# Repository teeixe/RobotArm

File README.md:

# RobotArm
Braço Robo de Cinco Articulações

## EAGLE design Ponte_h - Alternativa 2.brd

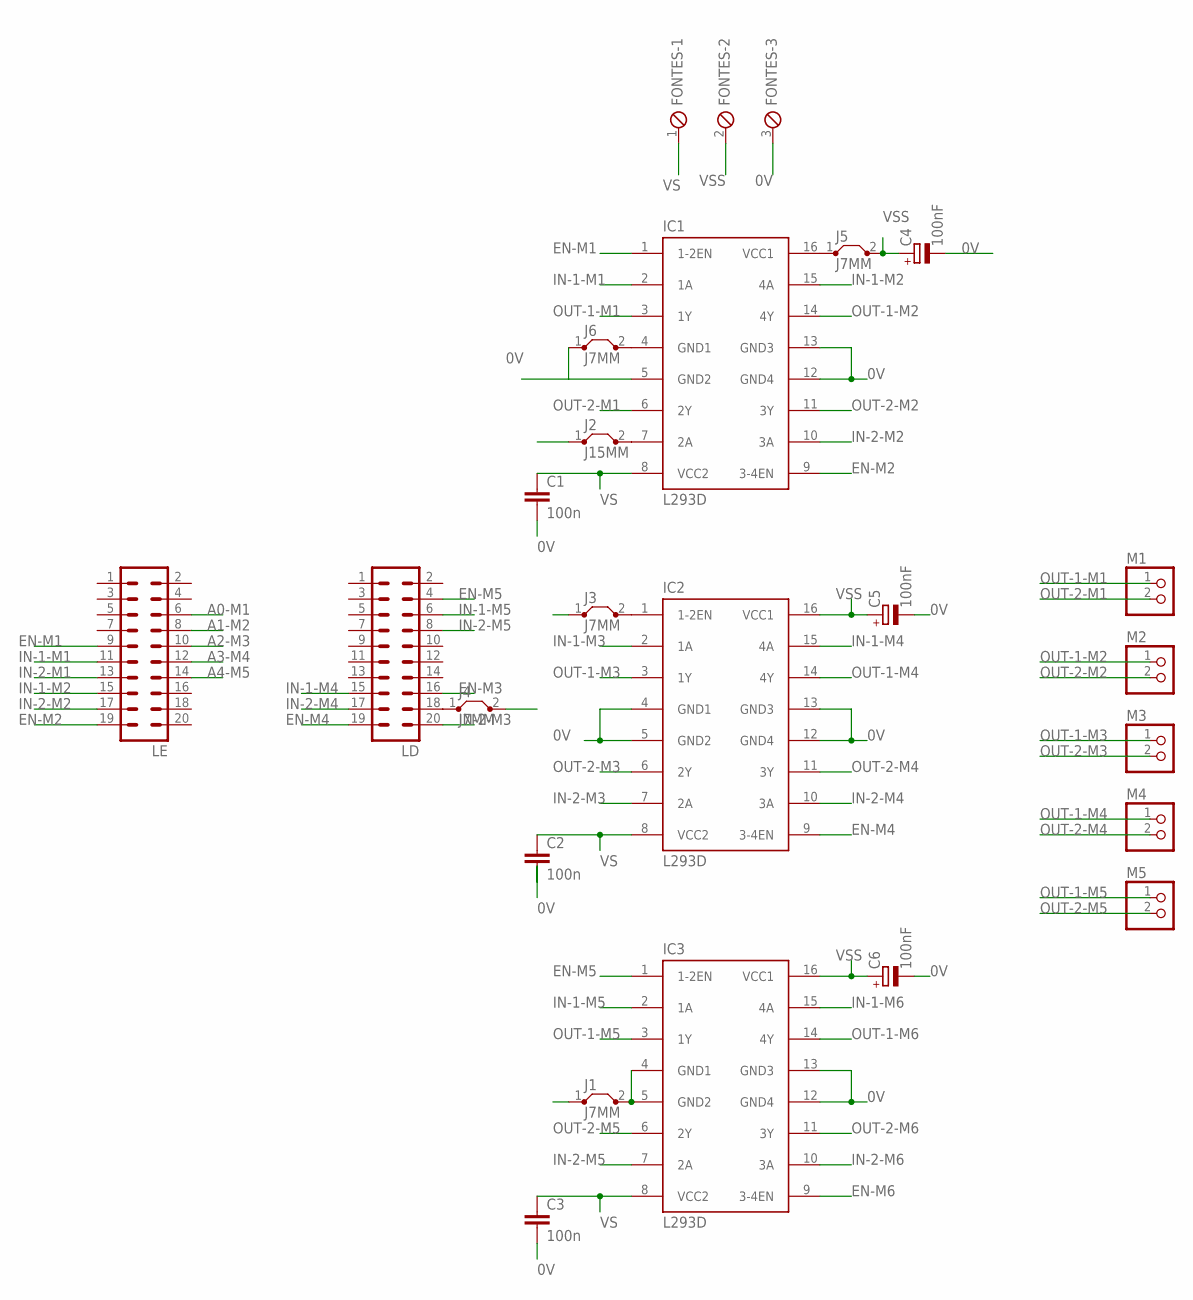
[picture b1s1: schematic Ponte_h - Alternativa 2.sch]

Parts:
C1, C2, C3: 100n; C7.5B3
C4, C5, C6: 100nF; E1,8-4
FONTES: MPT3; 3POL254
IC1, IC2, IC3: L293D; DIL16
J1, J3, J4, J5, J6: J7MM; 07
J2: J15MM; 15
LD: MA10-2
LE: MA10-2
M1, M2, M3, M4, M5: PINHD-1X2; 1X02

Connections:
0V: C1.2, C2.2, C3.2, C4.-, C5.-, C6.-, FONTES.3, IC1.5 (GND2), IC1.12 (GND4), IC1.13 (GND3), IC2.4 (GND1), IC2.5 (GND2), IC2.12 (GND4), IC2.13 (GND3), IC3.12 (GND4), IC3.13 (GND3), J1.1, J6.1
A0-M1: LE.6
A1-M2: LE.8
A2-M3: LE.10
A3-M4: LE.12
A4-M5: LE.14
EN-M1: IC1.1 (1-2EN), LE.9
EN-M2: IC1.9 (3-4EN), LE.19
EN-M3: J3.1, J4.2, LD.16
EN-M4: IC2.9 (3-4EN), LD.19
EN-M5: IC3.1 (1-2EN), LD.4
EN-M6: IC3.9 (3-4EN)
IN-1-M1: IC1.2 (1A), LE.11
IN-1-M2: IC1.15 (4A), LE.15
IN-1-M3: IC2.2 (1A)
IN-1-M4: IC2.15 (4A), LD.15
IN-1-M5: IC3.2 (1A), LD.6
IN-1-M6: IC3.15 (4A)
IN-2-M1: J2.1, LE.13
IN-2-M2: IC1.10 (3A), LE.17
IN-2-M3: IC2.7 (2A), LD.20
IN-2-M4: IC2.10 (3A), LD.17
IN-2-M5: IC3.7 (2A), LD.8
IN-2-M6: IC3.10 (3A)
unnamed: IC1.7 (2A), J2.2
unnamed: IC3.4 (GND1), IC3.5 (GND2), J1.2
unnamed: IC2.1 (1-2EN), J3.2
unnamed: J4.1, LD.18
unnamed: IC1.16 (VCC1), J5.1
unnamed: IC1.4 (GND1), J6.2
OUT-1-M1: IC1.3 (1Y), M1.1
OUT-1-M2: IC1.14 (4Y), M2.1
OUT-1-M3: IC2.3 (1Y), M3.1
OUT-1-M4: IC2.14 (4Y), M4.1
OUT-1-M5: IC3.3 (1Y), M5.1
OUT-1-M6: IC3.14 (4Y)
OUT-2-M1: IC1.6 (2Y), M1.2
OUT-2-M2: IC1.11 (3Y), M2.2
OUT-2-M3: IC2.6 (2Y), M3.2
OUT-2-M4: IC2.11 (3Y), M4.2
OUT-2-M5: IC3.6 (2Y), M5.2
OUT-2-M6: IC3.11 (3Y)
VS: C1.1, C2.1, C3.1, FONTES.1, IC1.8 (VCC2), IC2.8 (VCC2), IC3.8 (VCC2)
VSS: C4.+, C5.+, C6.+, FONTES.2, IC2.16 (VCC1), IC3.16 (VCC1), J5.2

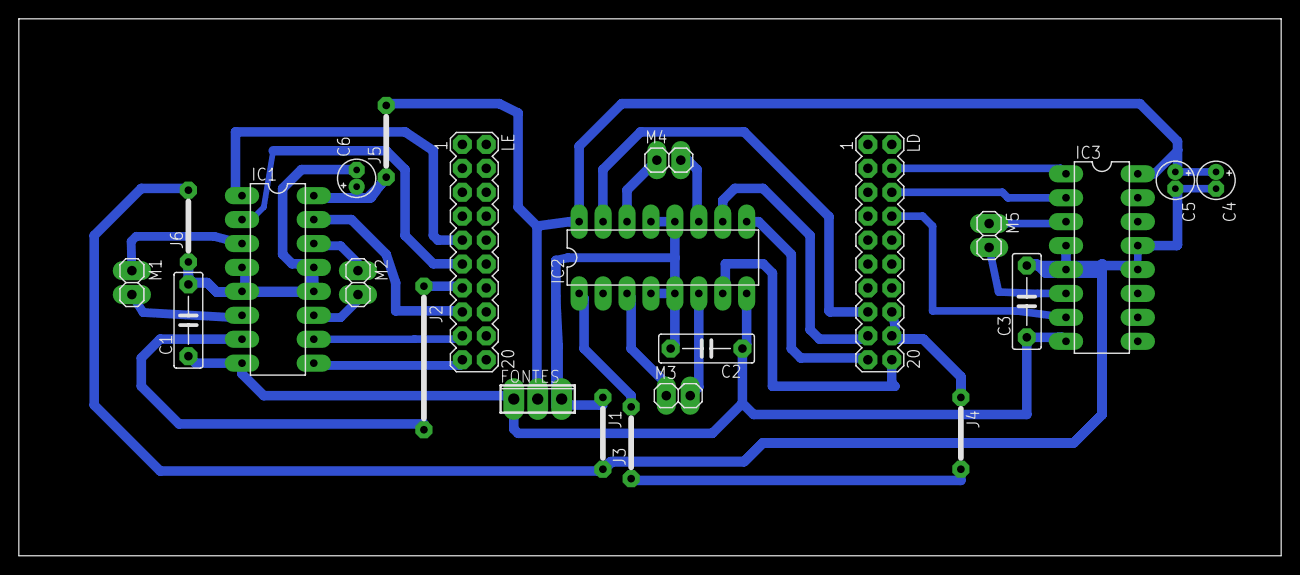
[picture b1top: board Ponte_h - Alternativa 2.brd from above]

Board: 2 copper layers, 134.0 x 57.0 mm, 23 parts (0 on the bottom side), 33 nets.

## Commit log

2016-05-21 Firt Version of code
2016-05-21 Segunda Versão para Teste de 1 Motor
2016-05-21 Versão para teste de 1 motor
2016-05-22 Configurado a Matriz de SetPoint para o Motor 1,
2016-05-22 Configurado Matriz para SetPoint para 1 motor Falta corrigir delay time
2016-05-22 Alterado a maquina de estados para switch case Falta fazer o teste prático
2016-07-01 Versão com 4 motores funcionando - 5 posições
    Motores M1, M2, M3 e M5 funcionando.
